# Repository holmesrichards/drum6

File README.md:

# drum6
Ridiculous bending and repurposing of First Act drum pad as Eurorack module and maybe controller

I paid $5 at a thrift store for a First Act Discovery Monsta Jam Digital Drum Pad toy. I'm working on bending it and repurposing its guts as a Eurorack module, and I might turn the externals into a synth controller too.

The main board allows generating six predefined drum sounds. These will be triggerable in the module. The speed/pitch also turns out to be voltage controllable, so there'll be a CV input for that. Annoyingly, it times itself out after a certain amount of inactivity, and this doesn't seem to be preventable. But I plan to add a circuit to poke it awake again every time it drifts off, kind of like you do when your grandfather is driving.

The obnoxious canned rhythms will not be made available.

This will be the sort of drum module no one wants, but it'll be fun making it.

Meanwhile the externals, including the pads themselves and the associated switches, are usable and might become a trigger/gate generating controller.

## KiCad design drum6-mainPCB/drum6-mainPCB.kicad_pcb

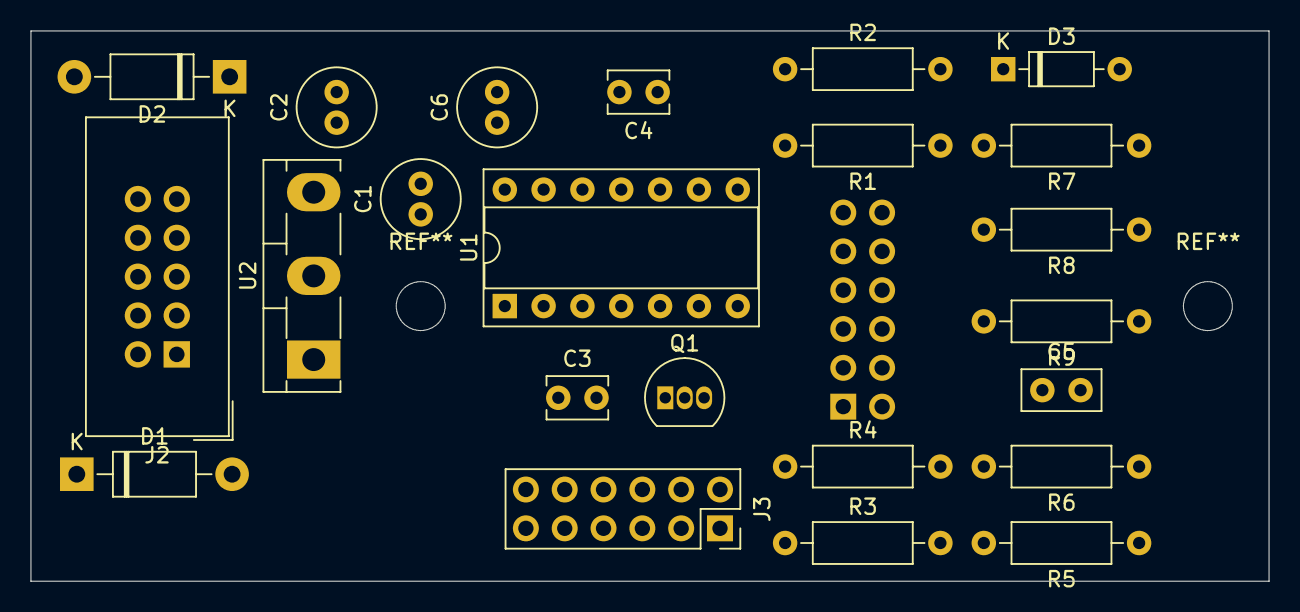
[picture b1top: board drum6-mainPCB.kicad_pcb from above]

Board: 2 copper layers, 81.0 x 36.0 mm, 24 parts (1 on the bottom side), 25 nets, no tracks yet.

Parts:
C1, C2, C6: 10U; C_Radial_D5.0mm_H11.0mm_P2.00mm
C3, C4: 0.01U; C_Disc_D3.8mm_W2.6mm_P2.50mm
C5: 0.1u; C_Disc_D5.0mm_W2.5mm_P2.50mm
D1, D2: 1N5817; D_DO-41_SOD81_P10.16mm_Horizontal
D3: 1N4148; D_DO-35_SOD27_P7.62mm_Horizontal
J1: Conn_02x06_Odd_Even; PinHeader_2x06_P2.54mm_Vertical
J2: EURO_PWR_2x5; IDC-Header_2x05_P2.54mm_Vertical
J3: Conn_02x06_Odd_Even; PinSocket_2x06_P2.54mm_Vertical
Q1: 2N3904; TO-92_Inline
R1, R2, R3, R4: 100k; R_Axial_DIN0207_L6.3mm_D2.5mm_P10.16mm_Horizontal
R5, R6: 1k; R_Axial_DIN0207_L6.3mm_D2.5mm_P10.16mm_Horizontal
R7: 47k; R_Axial_DIN0207_L6.3mm_D2.5mm_P10.16mm_Horizontal
R8, R9: 47K; R_Axial_DIN0207_L6.3mm_D2.5mm_P10.16mm_Horizontal
U1: TL074; DIP-14_W7.62mm_Socket
U2: L7805; TO-218-3_Vertical

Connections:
/+12V: D1.1, J2.1, J2.2
/-12V: D2.2, J2.9, J2.10
/TRIG1_M: J1.2, J3.2
/TRIG2_M: J1.4, J3.4
/TRIG3_M: J1.6, J3.6
/TRIG4_M: J1.8, J3.8
/TRIG5_M: J1.10, J3.10
/TRIG6_M: J1.12, J3.12
AUDIO: J3.5, R8.2
CVB: J3.3, R3.1, R4.1
CVIN: J1.1, R3.2
CVOFFS: J1.3, R4.2
GND: C1.2, C2.1, C3.1, C4.2, C6.2, D3.2, J1.11, J2.3, J2.4, J2.5, J2.6, J2.7, J2.8, J3.11, Q1.1, R2.1, R6.1, R7.1, U1.3, U2.2
unnamed: C1.1, C3.2, D1.2, U1.4, U2.1
unnamed: C2.2, C4.1, D2.1, U1.11
unnamed: C5.1, D3.1, R7.2, U1.10
unnamed: C5.2, R5.1, R6.2
unnamed: Q1.2, U1.8, U1.9
unnamed: R1.1, R2.2, U1.5
unnamed: R5.2, U1.7
unnamed: R8.1, R9.2, U1.2
OUT: J1.7, R9.1, U1.1
REST: J3.1, Q1.3
STATUS: J3.7, U1.6
VCC: C6.1, J1.9, J3.9, R1.2, U2.3

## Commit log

2020-02-23 Initial version
2020-02-23 Better CV and better wake-up idea described
2020-02-23 Move licensing
2020-02-23 Create LICENSE
2020-02-26 KiCad directories
2020-02-26 More cruft
2020-02-26 New developments
2020-02-29 I have a cunning plan
2021-01-17 Include lib table files
